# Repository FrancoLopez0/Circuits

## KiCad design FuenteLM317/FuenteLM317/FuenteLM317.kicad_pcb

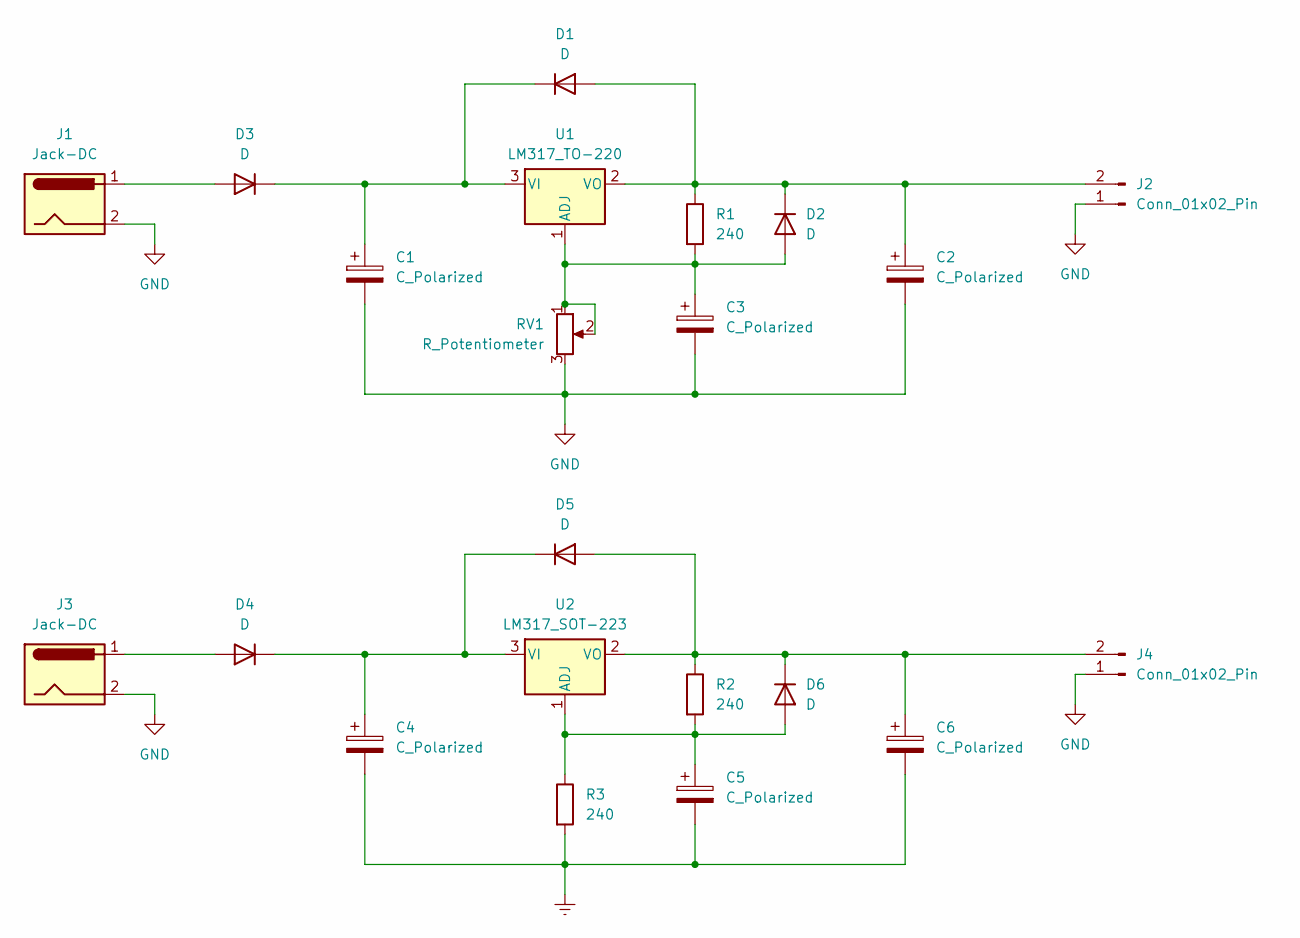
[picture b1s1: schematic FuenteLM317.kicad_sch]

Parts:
C1, C2, C3, C4, C5, C6: C_Polarized; CP_Radial_D10.0mm_P3.80mm
D1, D2, D3: D; D_5W_P12.70mm_Horizontal
D4, D5, D6: D; D_SOD-123
J1, J3: Jack-DC; BarrelJack_SwitchcraftConxall_RAPC10U_Horizontal
J2, J4: Conn_01x02_Pin; Molex_Micro-Latch_53253-0270_1x02_P2.00mm_Vertical
R1: 240; R_Axial_DIN0411_L9.9mm_D3.6mm_P15.24mm_Horizontal
R2, R3: 240; R_MiniMELF_MMA-0204
RV1: R_Potentiometer; Potentiometer_Alps_RK163_Single_Horizontal
U1: LM317_TO-220; TO-220-3_Vertical
U2: LM317_SOT-223; SOT-223-3_TabPin2

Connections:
Earth: C4.2, C5.2, C6.2, R3.2
GND: C1.2, C2.2, C3.2, J1.2, J2.1, J3.2, J4.1, RV1.3
unnamed: C2.1, D1.2 (A), D2.1 (K), J2.2, R1.1, U1.2 (VO)
unnamed: C1.1, D1.1 (K), D3.1 (K), U1.3 (VI)
unnamed: C3.1, D2.2 (A), R1.2, RV1.1, RV1.2, U1.1 (ADJ)
unnamed: D3.2 (A), J1.1
unnamed: D4.2 (A), J3.1
unnamed: C4.1, D4.1 (K), D5.1 (K), U2.3 (VI)
unnamed: C6.1, D5.2 (A), D6.1 (K), J4.2, R2.1, U2.2 (VO)
unnamed: C5.1, D6.2 (A), R2.2, R3.1, U2.1 (ADJ)

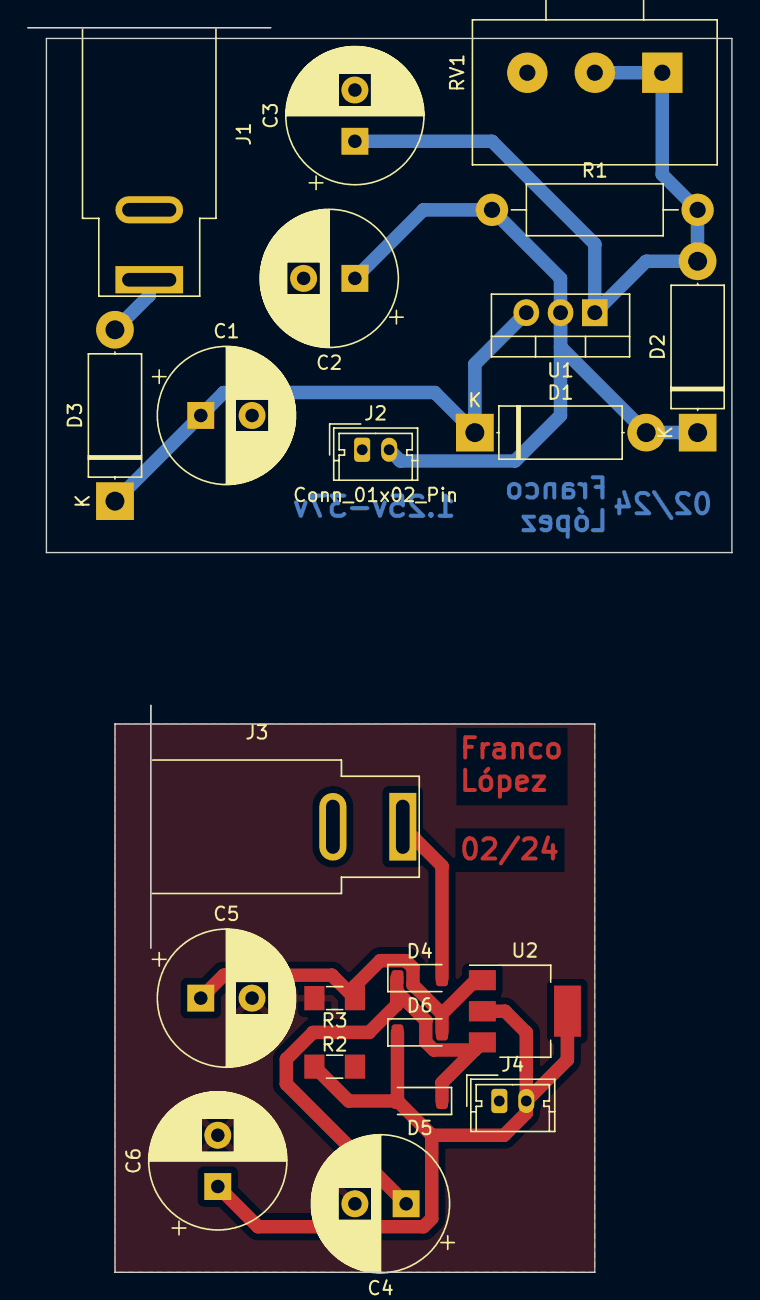
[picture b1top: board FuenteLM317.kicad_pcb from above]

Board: 2 copper layers, 52.2 x 92.2 mm, 22 parts (0 on the bottom side), 10 nets.

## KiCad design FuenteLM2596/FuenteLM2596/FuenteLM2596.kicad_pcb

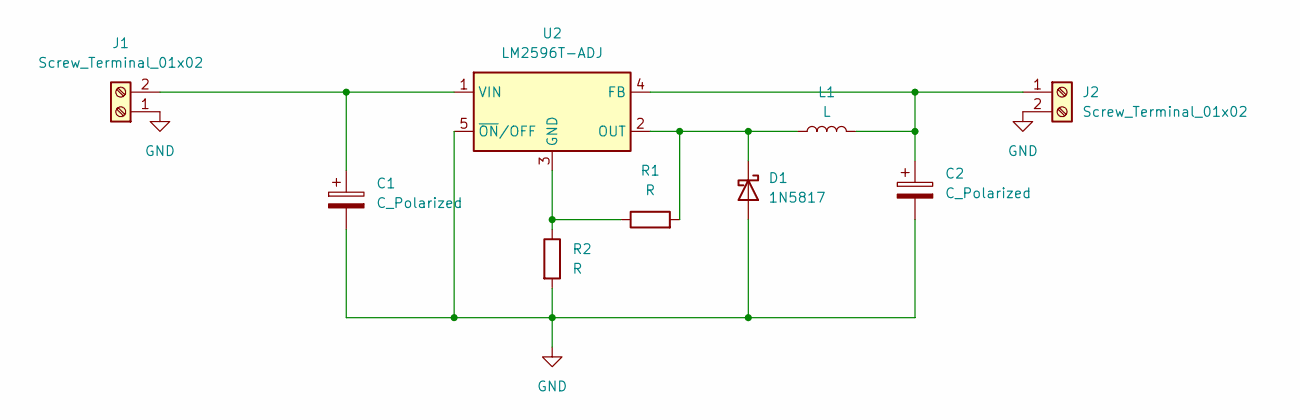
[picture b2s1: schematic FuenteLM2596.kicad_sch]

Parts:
C1, C2: C_Polarized; CP_Radial_D10.0mm_P3.80mm
D1: 1N5817; D_DO-41_SOD81_P10.16mm_Horizontal
J1, J2: Screw_Terminal_01x02; TerminalBlock_MetzConnect_Type059_RT06302HBWC_1x02_P3.50mm_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
L1: L; L_Axial_L5.3mm_D2.2mm_P2.54mm_Vertical_Vishay_IM-1
R1, R2: R; R_Axial_DIN0204_L3.6mm_D1.6mm_P7.62mm_Horizontal
U2: LM2596T-ADJ; TO-220-5_P3.4x3.7mm_StaggerOdd_Lead3.8mm_Vertical

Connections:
GND: C1.2, C2.2, D1.2 (A), J1.1, J2.2, R2.2, U2.5 (~ON/OFF)
unnamed: D1.1 (K), L1.1, R1.2, U2.2 (OUT)
unnamed: C1.1, J1.2, U2.1 (VIN)
unnamed: C2.1, J2.1, L1.2, U2.4 (FB)
unnamed: R1.1, R2.1, U2.3 (GND)

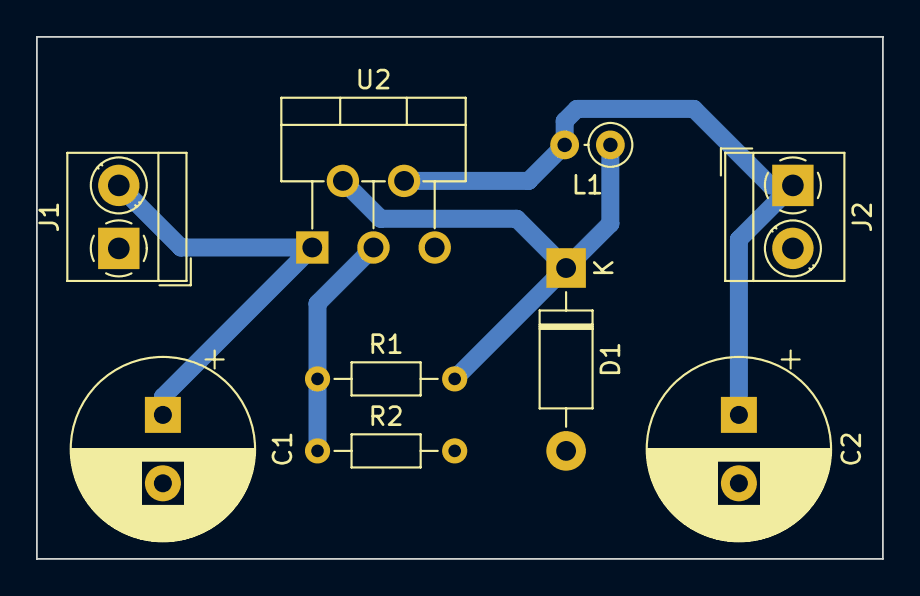
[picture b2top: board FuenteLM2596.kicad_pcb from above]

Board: 2 copper layers, 47.0 x 29.0 mm, 9 parts (0 on the bottom side), 5 nets.

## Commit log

2024-09-02 Init
